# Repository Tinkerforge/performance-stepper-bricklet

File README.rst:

Performance Stepper Bricklet
============================

**This Bricklet is currently in development.**

This repository contains the firmware source code and the hardware design
files. The documentation generator configs can be found at
https://github.com/Tinkerforge/generators

Repository Content
------------------

software/:
 * examples/: Examples for all supported languages
 * build/: Compiled files
 * src/: Source code of firmware
 * Makefile: Makefile to build project

hardware/:
 * Contains KiCad project files and additionally schematics as PDF

datasheets/:
 * Contains datasheets for sensors and complex ICs that are used

Hardware
--------

The hardware is designed with the open source EDA Suite KiCad
(http://www.kicad.org). Before you are able to open the files,
you have to install the Tinkerforge kicad-libraries
(https://github.com/Tinkerforge/kicad-libraries). You can either clone
them directly in hardware/ or clone them in a separate folder and
symlink them into hardware/
(ln -s kicad_path/kicad-libraries project_path/hardware). After that you
can open the .pro file in hardware/ with KiCad and from there view and
modify the schematics and the PCB layout.

Software
--------

If you want to do your own Brick/Bricklet firmware development we highly
recommend that you use our build environment setup script and read the
tutorial (https://www.tinkerforge.com/en/doc/Tutorials/Tutorial_Build_Environment/Tutorial.html).

To compile the C code we recommend you to install the newest GNU Arm Embedded
Toolchain (https://launchpad.net/gcc-arm-embedded/+download).
You also need to install bricklib2 (https://github.com/Tinkerforge/bricklib2).

You can either clone it directly in software/src/ or clone it in a
separate folder and symlink it into software/src/
(ln -s bricklib_path/bricklib2 project_path/software/src/). Finally make sure to
have CMake installed (http://www.cmake.org/cmake/resources/software.html).

After that you can build the firmware by invoking make in software/.
The firmware (.zbin) can then be found in software/build/ and uploaded
with brickv (click button "Flashing" on start screen).

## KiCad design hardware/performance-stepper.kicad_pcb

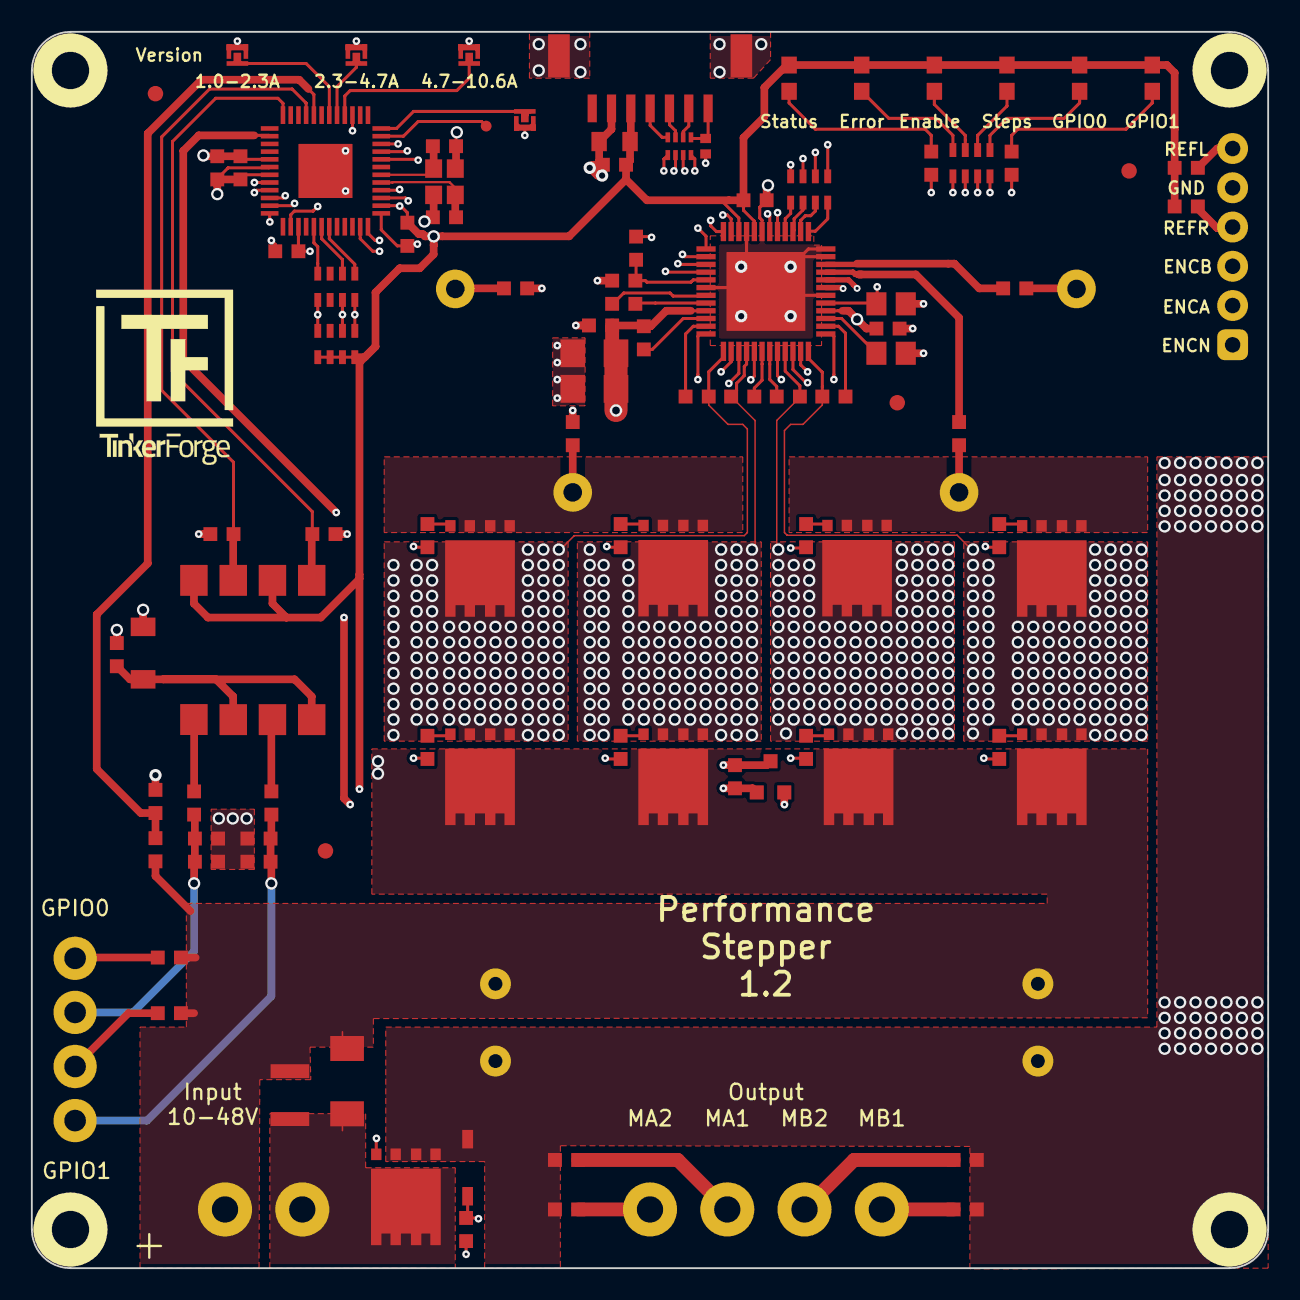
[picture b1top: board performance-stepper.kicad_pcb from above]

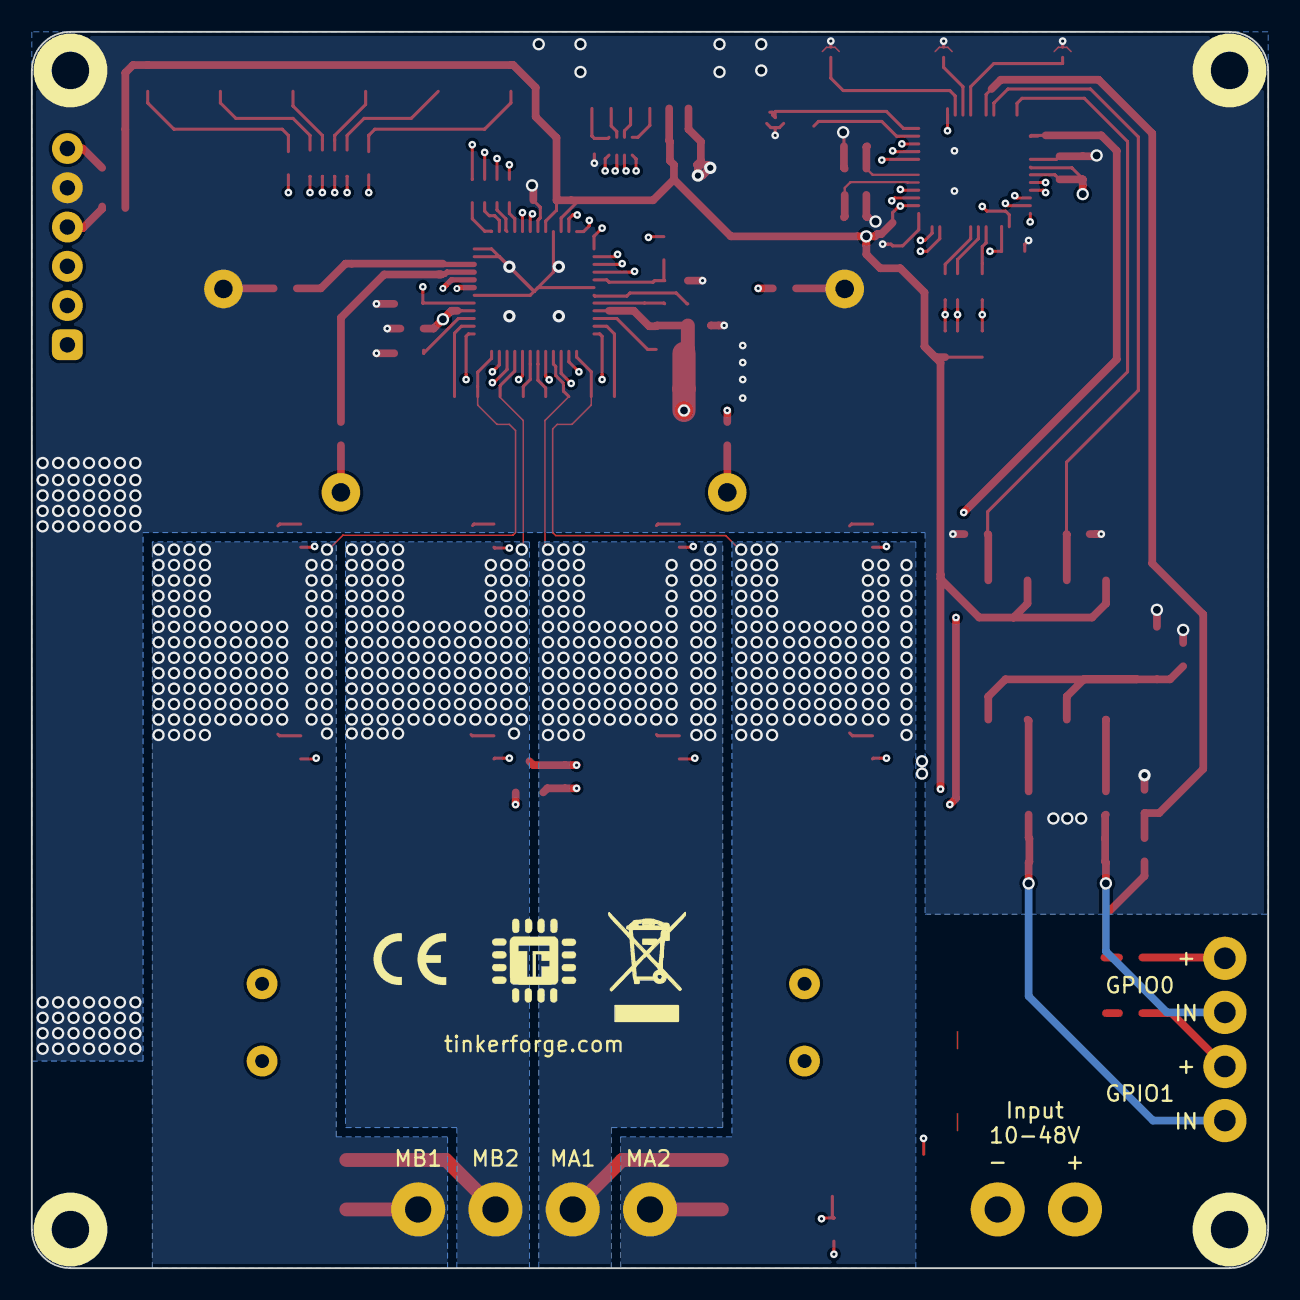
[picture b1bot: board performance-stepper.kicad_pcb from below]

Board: 4 copper layers, 80.0 x 80.0 mm, 112 parts (2 on the bottom side), 98 nets.

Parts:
C1, C4: 10pF; C0603F
C2, C9, C19, C30, C104: 100nF; C0603F
C3: 220nF; C0603F
C5, C11, C12, C23, C24, C25: 100nF/100V; C0603F
C6, C7: 2,2uF/16V; C0805E
C8, C13, C14, C15, C16: 470nF/25V; C0603F
C10: 22nF/100V; C0603F
C17, C18: 2,2uF/100V; C1206E
C20, C21: 220uF/100V/UVY2A221MHD1TO; ELKO_RAD_12
C26, C27, C28, C29: 1nF/100V; C0603F
C101: 10uF; C0805
C102: 220pF; C0402F
C103: 1uF; C0603F
D1: Z12V; SOD-123
D2: Z3,3V; MiniMelf
D3: red; D0603E
D4, D5, D6, D7, D101: blue; D0603E
D8: SMBJ48CA; SMB
Fiducial_Mark: VAL**; Fiducial_Mark
Fiducial_Mark#2, Fiducial_Mark#3, Fiducial_Mark#4: VAL**; Fiducial_Mark
P1: VIN; OQ_2P_5mm_Vertical_Black
P2: OUT; OQ_4P_5mm_Vertical
P3: GPIO; OQ_4P_Vertical
P4: PROTO; pin_array_1x6-P2mm_D1mm
P5: L; SolderJumper
P6: M; SolderJumper
P7: S; SolderJumper
P101: CON-SENSOR2; CON-SENSOR2_180
P102: DEBUG; DEBUG_PAD
P103: BOOT; SolderJumper
Q1, Q2, Q3, Q4, Q5, Q6, Q7, Q8, Q9: CSD19533Q5A; SON_5x6mm
R1: 2,2; R0603F
R2, R3, R4, R5, R12, R13, R14, R15: 10; R0603F
R6, R7, R8, R9: 47; R0603F
R10, R11: DNP; MSR-3
R16: 100k; R0603F
R17, R18, R19, R20, R25, R26: 1k; R0603F
R21, R22: 4,7k; R0603F
R23, R24: 2,2k; R0603F
R27: 10k; R0603F
R28: 150k; R0603F
R29: VG121048H101DP; 1210
R30, R31: DNP; R0603F
RP1: 10k; 0603X4
RP2: 22; 4X0603
RP3: 22; 0603X4
RP4: 1k; 0603X4
RP101: 82; 4X0402
U1: TMC5160A; eTQFP-48_7x7mm
U2: XMC1404; QFN48-EP2
U3: LTV-827; DIP_8_SMD
U4: TMP235; SOT23-3
U103, U104, U105, U106: DRILL; DRILL_NP
VAL: WEEE_7mm
VAL#2: CE_5mm
X1: 16MHz; CRYSTAL_2520

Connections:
CS_TMC: RP2.4, U2.40
DIAG0: RP3.2, U2.30
DIAG1: RP3.1, U2.31
DRV_ENN: RP3.4, U2.29
GND: C1.2, C2.2, C3.2, C4.2, C5.2, C6.1, C7.1, C8.1, C9.2, C12.2, C17.2, C18.2, C19.2, C20.2, C21.2, C23.2, C24.2, C25.2, C26.2, C27.1, C28.2, C29.1, C30.2, C101.1, C102.1, C103.1, C104.2, D1.1, D2.1, P4.5, P5.1, P6.1, P7.1, P101.2, P101.EP, P103.1, Q9.S, R7.1, R9.1, R10.1, R11.1, R17.1, R18.1, R21.1, R22.1, R27.1, U1.6, U1.11, U1.12, U1.19, U1.21, U1.30, U1.49, U2.17, U2.37, U2.EP, U4.3, X1.3
GPIO0: R17.2, U2.9, U3.7
GPIO1: R18.2, U2.12, U3.5
MISO_TMC: RP2.1, U2.35
MOSI_TMC: RP2.2, U2.36
unnamed: C1.1, U2.41, X1.1
unnamed: C4.1, U2.42, X1.2
unnamed: C6.2, U1.3
unnamed: C7.2, R1.2, U1.5
unnamed: C8.2, R1.1, U1.29
unnamed: C10.1, U1.31
unnamed: C10.2, U1.32
unnamed: C11.2, U1.34
unnamed: C13.1, C28.1, P2.3, Q5.S, Q6.D, U1.45
unnamed: C13.2, U1.43
unnamed: C14.1, C26.1, P2.4, Q1.S, Q2.D, U1.48
unnamed: C14.2, U1.2
unnamed: C15.1, C27.2, P2.1, Q7.S, Q8.D, U1.37
unnamed: C15.2, U1.35
unnamed: C16.1, C29.2, P2.2, Q3.S, Q4.D, U1.40
unnamed: C16.2, U1.42
unnamed: C23.1, D2.2, U3.2, U3.4
unnamed: C24.1, P3.2, R19.1, R21.2
unnamed: C25.1, P3.4, R20.1, R22.2
unnamed: C102.2, P101.7, RP101.5
unnamed: D1.2, Q9.G, R16.1
unnamed: D3.2, RP4.4
unnamed: D4.2, RP4.1
unnamed: D5.2, R25.1
unnamed: D6.2, RP4.2
unnamed: D7.2, RP4.3
unnamed: D8.2, P1.2, Q9.D, R29.2
unnamed: D101.2, R26.1
unnamed: P3.1, R23.1
unnamed: P3.3, R24.1
unnamed: P4.1, U1.25
unnamed: P4.2, U1.24
unnamed: P4.3, U1.23
unnamed: P4.4, R31.1, U1.18
unnamed: P4.6, R30.1, U1.17
unnamed: P5.2, U2.4
unnamed: P6.2, U2.5
unnamed: P7.2, U2.6
unnamed: P101.4, RP101.8
unnamed: P101.5, RP101.7
unnamed: P101.6, RP101.6
unnamed: P102.1, U2.47
unnamed: P103.2, U2.48
unnamed: Q1.G, R2.1
unnamed: Q2.G, R3.1
unnamed: Q2.S, Q6.S, R6.1, R10.2
unnamed: Q3.G, R4.1
unnamed: Q4.G, R5.1
unnamed: Q4.S, Q8.S, R8.1, R11.2
unnamed: Q5.G, R12.1
unnamed: Q6.G, R13.1
unnamed: Q7.G, R14.1
unnamed: Q8.G, R15.1
unnamed: R2.2, U1.1
unnamed: R3.2, U1.47
unnamed: R4.2, U1.41
unnamed: R5.2, U1.39
unnamed: R6.2, U1.9
unnamed: R7.2, U1.10
unnamed: R8.2, U1.8
unnamed: R9.2, U1.7
unnamed: R12.2, U1.44
unnamed: R13.2, U1.46
unnamed: R14.2, U1.36
unnamed: R15.2, U1.38
unnamed: R19.2, U3.1
unnamed: R20.2, U3.3
unnamed: R25.2, U2.20
unnamed: R26.2, U2.26
unnamed: RP1.5, RP3.8, U1.27
unnamed: RP1.6, RP3.7, U1.26
unnamed: RP1.8, RP3.5, U1.28
unnamed: RP2.5, U1.13
unnamed: RP2.6, U1.14
unnamed: RP2.7, U1.15
unnamed: RP2.8, U1.16
unnamed: RP4.5, U2.24
unnamed: RP4.6, U2.23
unnamed: RP4.7, U2.22
unnamed: RP4.8, U2.21
S-CLK: RP101.2, U2.45
S-CS: RP101.1, U2.44
S-MISO: RP101.4, U2.3
S-MOSI: RP101.3, U2.46
SCK_TMC: RP2.3, U2.39
TEMP: U2.14, U4.2
VCC: C2.1, C3.1, C9.1, C19.1, C30.1, C101.2, C103.2, C104.1, D3.1, D4.1, D5.1, D6.1, D7.1, D101.1, P101.3, R30.2, R31.2, RP1.1, RP1.2, RP1.3, RP1.4, U1.20, U1.22, U2.18, U2.19, U2.27, U2.38, U3.6, U3.8, U4.1
V_GPIO: C5.1, C11.1, C12.1, C17.1, C18.1, C20.1, C21.1, D8.1, P1.1, Q1.D, Q3.D, Q5.D, Q7.D, R16.2, R23.2, R24.2, R28.2, R29.1, U1.4, U1.33
V_Sense: R27.2, R28.1, U2.8

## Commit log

2019-11-22 Add auto-generated Silent Stepper Bricklet 2.0 firmware stub
2019-11-22 TCM -> TMC
2019-12-02 Add coop spi fifo support
2020-01-22 added schematic
2020-01-24 schematic and pcb changes
2020-01-29 pcb design
2020-01-31 finished prototype ready for revision
2020-02-03 changes protection circuit
2020-02-05 ready for prototype
2020-02-06 DRC control and ordered prototyp
2020-03-27 Add ifdef support for development board and prototype
2020-03-27 Add initial API
2020-03-27 Add TMC5160 registers and helper functions
2020-04-01 changed GPIO interrupt pin and added zener value
2020-04-02 added Voltage In Sense
2020-04-03 Add initial GPIO and voltage support
2020-04-03 Improve API
2020-04-06 Remove devboard support
2020-04-06 Add support for get_current_velocity
2020-04-06 Add basic GPIO support
2020-04-07 Add support for LED blinkenlights
2020-04-08 changed shunt resistors
2020-04-08 changed varistor value and footprint
2020-04-15 Add more value checks
2020-04-15 Convert 24 bit signed integer correctly
2020-04-15 TMC is enabled if enabled pin is low
2020-04-15 Scale delay time correctly
2020-04-15 Remove unused code and unavailable registers
    TODO: We need to remove random slow decay from API still
2020-04-15 Fix typos
2020-04-15 Make sure only one coop task can use read/write at the same time
2020-04-15 Fix overflow
2020-04-15 Add TMC5160 default configuration
    TODO:
    * Use sane default configuration that works in most cases
    * Detect if TMC5160 got unpowered
    * Write default configuration back to TMC5160 on startup and
    after unpower event
2020-05-08 changed resistor
2020-07-09 added Temperature Sensor, added pullups and ground to proto header, removed screwholes, moved 47 ohm inline resitors for better shunt clearance, removed no-silkscreen area on bottomlayer, removed big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
2020-07-14 changed resistor array footprint
2020-07-23 new hardware version
2020-08-06 changed C6, C7 footprint to 0805 and updated SON_5x6 footprint
2020-09-09 version 2.2 : changed name, added shunt version solderjumpers, moved pins for boot and debug pad, changed silkscreen
2020-09-09 changed silkscreen
2020-09-09 Add temperature measurements and update defaults
2020-09-09 changed version number, changed silkscreen
2020-09-14 Rename to "Performance Stepper Bricklet"
2020-10-14 updated all OQ connectors with new F.Fab layer
2021-10-25 Update KiCad link
    https://www.kicad.org/blog/2021/10/Avoid-links-to-former-kicad-domain/
2022-07-06 Add license files.
2025-10-04 Fix compatibility with new Docker build image (GCC 14.2.1)

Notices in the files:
hardware/performance-stepper.kicad_pcb:
Licensed under CERN OHL v.1.1
Copyright (©) 2020, T.Schneidermann
Copyright Tinkerforge GmbH 2020.
This documentation describes Open Hardware and is licensed under the
CERN OHL v. 1.1.
